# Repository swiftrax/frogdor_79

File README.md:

### I provide this keyboard without liability and without any guarantees regarding functionality, as expressed in the Creative Commons license under which all of these PCBs are licensed.

KiCad and Fusion360 files are included 

Tested Working on USB 2.0

QMK Can be found in my fork

# Supported Layouts

# Images
[Imgur Album](https://imgur.com/a/08Liv0p)

# Case
[M3 Spacers](https://www.mcmaster.com/94868a162) x 4 

[M3 Screws](https://www.mcmaster.com/93070a057) 1 pack 

Reccomended Manufacturers for cases: **Ponoko for Acrylic, SendCutSend for Metal** 

Plate x 1 3mm Acrylic 

Midlayer x 2 3mm Acrylic 

Backplate x 1 3mm Acrylic 

*Note if using an aluminum plate use O-rings as a spacer

# QMK
[Keyboard](https://github.com/swiftrax/qmk_firmware/tree/master/keyboards/frogdor)

`make frogdor:default`

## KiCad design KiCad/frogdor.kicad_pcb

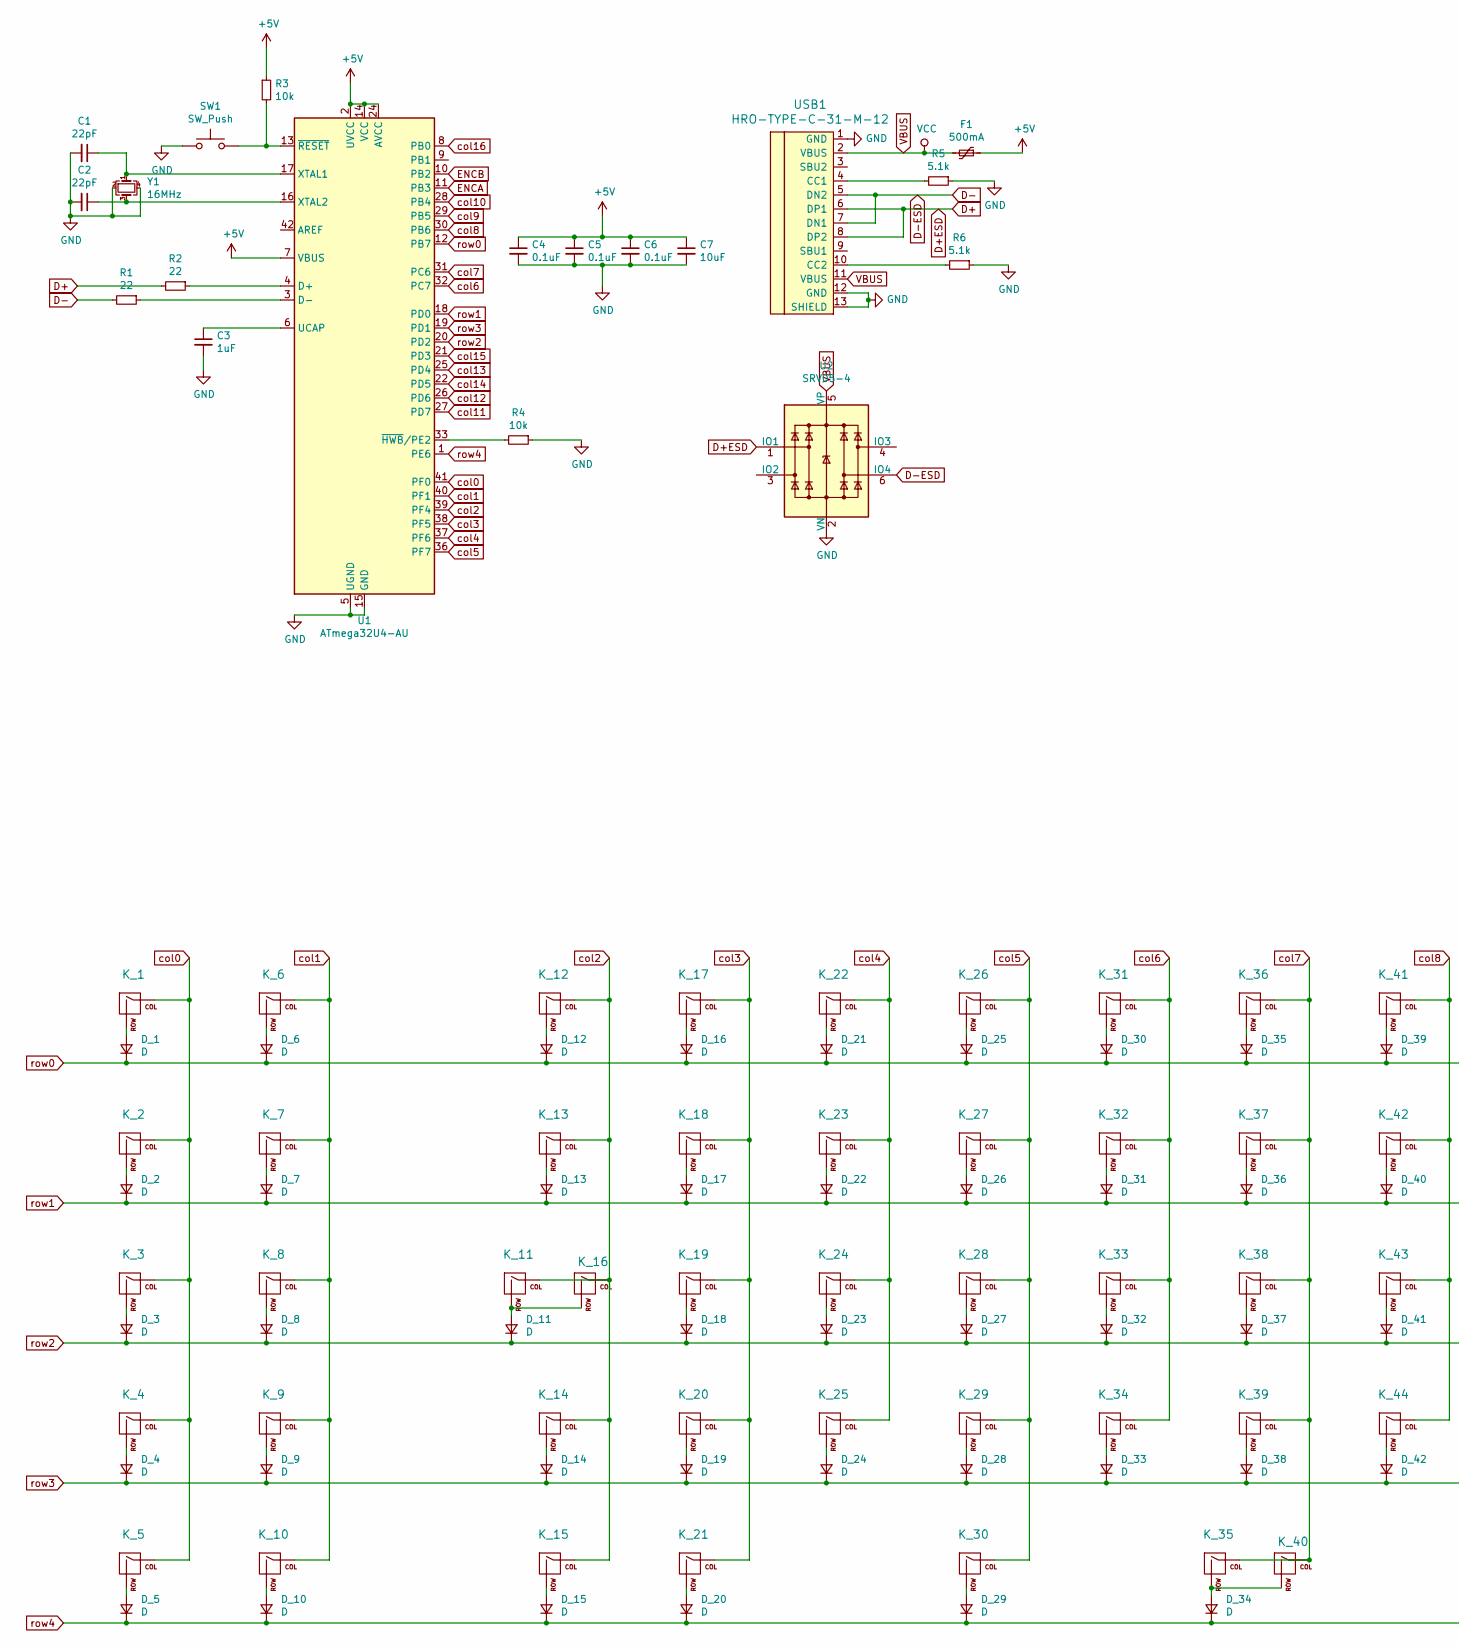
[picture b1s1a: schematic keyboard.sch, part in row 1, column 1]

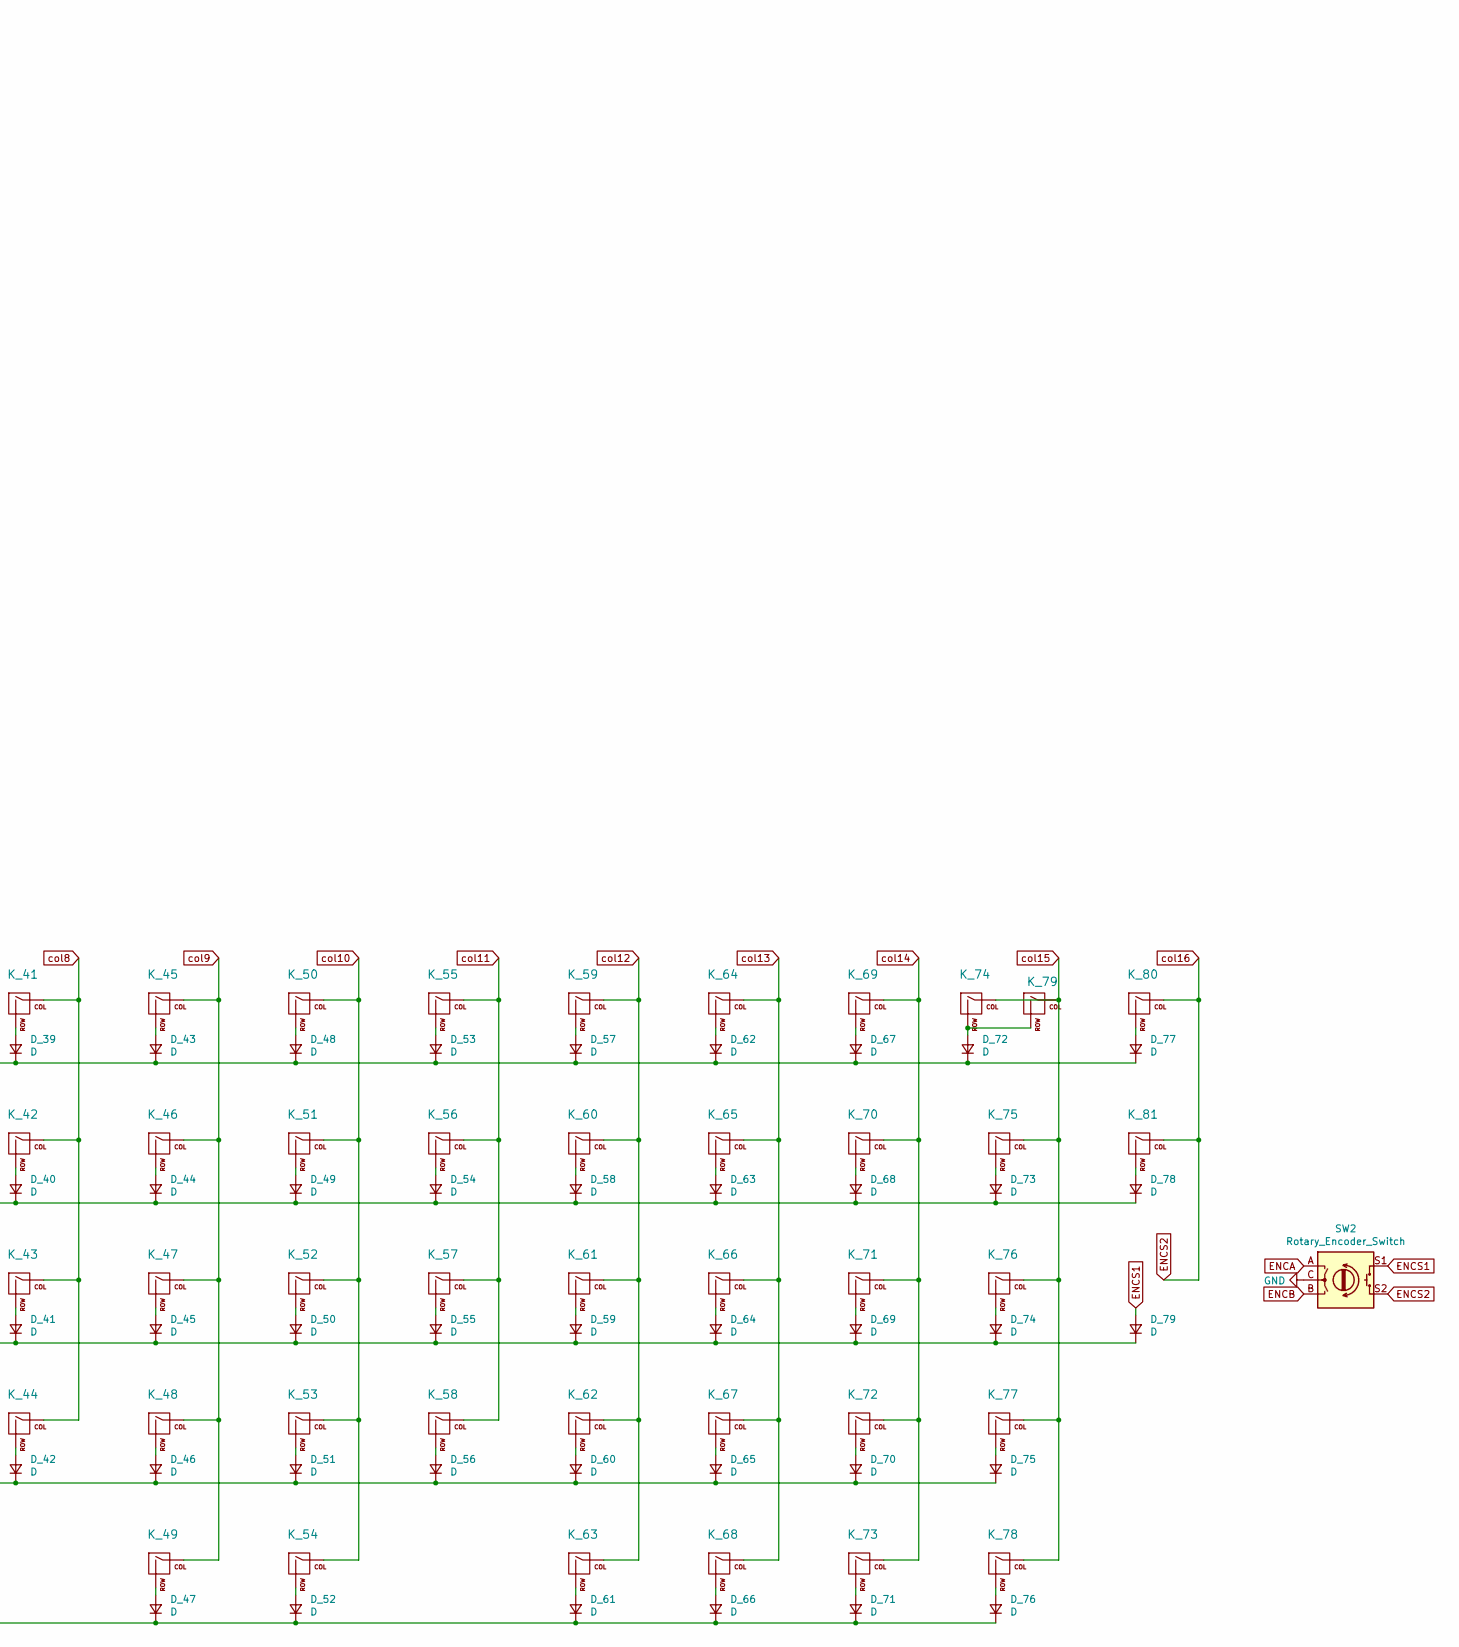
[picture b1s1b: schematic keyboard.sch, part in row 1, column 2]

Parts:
C1, C2: 22pF; C_0805_2012Metric
C3: 1uF; C_0805_2012Metric
C4, C5, C6: 0.1uF; C_0805_2012Metric
C7: 10uF; C_0805_2012Metric
D_1, D_2, D_3, D_4, D_5, D_6, D_7, D_8, D_9, D_10, D_11, D_12, D_13, D_14, D_15, D_16, D_17, D_18, D_19, D_20, D_21, D_22, D_23, D_24, D_25, D_26, D_27, D_28, D_29, D_30, D_31, D_32, D_33, D_34, D_35, D_36, D_37, D_38, D_39, D_40, D_41, D_42, D_43, D_44, D_45, D_46, D_47, D_48, D_49, D_50, D_51, D_52, D_53, D_54, D_55, D_56, D_57, D_58, D_59, D_60, D_61, D_62, D_63, D_64, D_65, D_66, D_67, D_68, D_69, D_70, D_71, D_72, D_73, D_74, D_75, D_76, D_77, D_78, D_79: D; D_SOD-123
F1: 500mA; Fuse_1206_3216Metric
K_1, K_2, K_3, K_4, K_5, K_6, K_7, K_8, K_9, K_10, K_12, K_17, K_18, K_19, K_20, K_22, K_23, K_24, K_25, K_26, K_27, K_28, K_29, K_31, K_32, K_33, K_34, K_36, K_37, K_38, K_39, K_41, K_42, K_43, K_44, K_45, K_46, K_47, K_48, K_50, K_51, K_52, K_53, K_55, K_56, K_57, K_58, K_59, K_60, K_61, K_62, K_64, K_65, K_66, K_68, K_69, K_70, K_72, K_73, K_74, K_76, K_77, K_78, K_80, K_81: KEYSW; MXOnly-1U-NoLED
K_11, K_15, K_21, K_35, K_54, K_63: KEYSW; MXOnly-1.25U-NoLED
K_13, K_75: KEYSW; MXOnly-1.5U-NoLED
K_14, K_49, K_71: KEYSW; MXOnly-2.25U-NoLED
K_16: KEYSW; MXOnly-1.75U-NoLED
K_30: KEYSW; MXOnly-2.75U-NoLED
K_40: KEYSW; MXOnly-6.25U-NoLED
K_67, K_79: KEYSW; MXOnly-2U-NoLED
R1, R2: 22; R_0805_2012Metric
R3, R4: 10k; R_0805_2012Metric
R5, R6: 5.1k; R_0805_2012Metric
SW1: SW_Push; SKQG-1155865
SW2: Rotary_Encoder_Switch; RotaryEncoder_EC11
U1: ATmega32U4-AU; TQFP-44_10x10mm_P0.8mm
U2: SRV05-4; SOT-23-6
USB1: HRO-TYPE-C-31-M-12; HRO-TYPE-C-31-M-12-HandSoldering
Y1: 16MHz; Crystal_SMD_3225-4Pin_3.2x2.5mm

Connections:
+5V: C4.1, C5.1, C6.1, C7.1, F1.1, R3.1, U1.2 (UVCC), U1.7 (VBUS), U1.14 (VCC), U1.24 (AVCC), U1.34 (VCC), U1.44 (AVCC)
D+: R2.2, U2.1 (IO1), USB1.6 (DP1), USB1.8 (DP2)
D-: R1.2, U2.6 (IO4), USB1.5 (DN2), USB1.7 (DN1)
ENCA: SW2.A, U1.11 (PB3)
ENCB: SW2.B, U1.10 (PB2)
ENCS1: D_79.2 (A), SW2.S1
ENCS2: K_80.1 (COL), K_81.1 (COL), SW2.S2, U1.8 (PB0)
GND: C1.2, C2.2, C3.2, C4.2, C5.2, C6.2, C7.2, R4.1, R5.1, R6.1, SW1.1, SW2.C, U1.5 (UGND), U1.15 (GND), U1.23 (GND), U1.35 (GND), U1.43 (GND), U2.2 (VN), USB1.1 (GND), USB1.12 (GND), USB1.13 (SHIELD), Y1.2, Y1.4
unnamed: C1.1, U1.17 (XTAL1), Y1.1
unnamed: C2.1, U1.16 (XTAL2), Y1.3
unnamed: C3.1, U1.6 (UCAP)
unnamed: D_1.2 (A), K_1.2 (ROW)
unnamed: D_2.2 (A), K_2.2 (ROW)
unnamed: D_3.2 (A), K_3.2 (ROW)
unnamed: D_4.2 (A), K_4.2 (ROW)
unnamed: D_5.2 (A), K_5.2 (ROW)
unnamed: D_6.2 (A), K_6.2 (ROW)
unnamed: D_7.2 (A), K_7.2 (ROW)
unnamed: D_8.2 (A), K_8.2 (ROW)
unnamed: D_9.2 (A), K_9.2 (ROW)
unnamed: D_10.2 (A), K_10.2 (ROW)
unnamed: D_11.2 (A), K_11.2 (ROW), K_16.2 (ROW)
unnamed: D_12.2 (A), K_12.2 (ROW)
unnamed: D_13.2 (A), K_13.2 (ROW)
unnamed: D_14.2 (A), K_14.2 (ROW)
unnamed: D_15.2 (A), K_15.2 (ROW)
unnamed: D_16.2 (A), K_17.2 (ROW)
unnamed: D_17.2 (A), K_18.2 (ROW)
unnamed: D_18.2 (A), K_19.2 (ROW)
unnamed: D_19.2 (A), K_20.2 (ROW)
unnamed: D_20.2 (A), K_21.2 (ROW)
unnamed: D_21.2 (A), K_22.2 (ROW)
unnamed: D_22.2 (A), K_23.2 (ROW)
unnamed: D_23.2 (A), K_24.2 (ROW)
unnamed: D_24.2 (A), K_25.2 (ROW)
unnamed: D_25.2 (A), K_26.2 (ROW)
unnamed: D_26.2 (A), K_27.2 (ROW)
unnamed: D_27.2 (A), K_28.2 (ROW)
unnamed: D_28.2 (A), K_29.2 (ROW)
unnamed: D_29.2 (A), K_30.2 (ROW)
unnamed: D_30.2 (A), K_31.2 (ROW)
unnamed: D_31.2 (A), K_32.2 (ROW)
unnamed: D_32.2 (A), K_33.2 (ROW)
unnamed: D_33.2 (A), K_34.2 (ROW)
unnamed: D_34.2 (A), K_35.2 (ROW), K_40.2 (ROW)
unnamed: D_35.2 (A), K_36.2 (ROW)
unnamed: D_36.2 (A), K_37.2 (ROW)
unnamed: D_37.2 (A), K_38.2 (ROW)
unnamed: D_38.2 (A), K_39.2 (ROW)
unnamed: D_39.2 (A), K_41.2 (ROW)
unnamed: D_40.2 (A), K_42.2 (ROW)
unnamed: D_41.2 (A), K_43.2 (ROW)
unnamed: D_42.2 (A), K_44.2 (ROW)
unnamed: D_43.2 (A), K_45.2 (ROW)
unnamed: D_44.2 (A), K_46.2 (ROW)
unnamed: D_45.2 (A), K_47.2 (ROW)
unnamed: D_46.2 (A), K_48.2 (ROW)
unnamed: D_47.2 (A), K_49.2 (ROW)
unnamed: D_48.2 (A), K_50.2 (ROW)
unnamed: D_49.2 (A), K_51.2 (ROW)
unnamed: D_50.2 (A), K_52.2 (ROW)
unnamed: D_51.2 (A), K_53.2 (ROW)
unnamed: D_52.2 (A), K_54.2 (ROW)
unnamed: D_53.2 (A), K_55.2 (ROW)
unnamed: D_54.2 (A), K_56.2 (ROW)
unnamed: D_55.2 (A), K_57.2 (ROW)
unnamed: D_56.2 (A), K_58.2 (ROW)
unnamed: D_57.2 (A), K_59.2 (ROW)
unnamed: D_58.2 (A), K_60.2 (ROW)
unnamed: D_59.2 (A), K_61.2 (ROW)
unnamed: D_60.2 (A), K_62.2 (ROW)
unnamed: D_61.2 (A), K_63.2 (ROW)
unnamed: D_62.2 (A), K_64.2 (ROW)
unnamed: D_63.2 (A), K_65.2 (ROW)
unnamed: D_64.2 (A), K_66.2 (ROW)
unnamed: D_65.2 (A), K_67.2 (ROW)
unnamed: D_66.2 (A), K_68.2 (ROW)
unnamed: D_67.2 (A), K_69.2 (ROW)
unnamed: D_68.2 (A), K_70.2 (ROW)
unnamed: D_69.2 (A), K_71.2 (ROW)
unnamed: D_70.2 (A), K_72.2 (ROW)
unnamed: D_71.2 (A), K_73.2 (ROW)
unnamed: D_72.2 (A), K_74.2 (ROW), K_79.2 (ROW)
unnamed: D_73.2 (A), K_75.2 (ROW)
unnamed: D_74.2 (A), K_76.2 (ROW)
unnamed: D_75.2 (A), K_77.2 (ROW)
unnamed: D_76.2 (A), K_78.2 (ROW)
unnamed: D_77.2 (A), K_80.2 (ROW)
unnamed: D_78.2 (A), K_81.2 (ROW)
unnamed: R1.1, U1.3 (D-)
unnamed: R2.1, U1.4 (D+)
unnamed: R3.2, SW1.2, U1.13 (~RESET)
unnamed: R4.2, U1.33 (~HWB~/PE2)
unnamed: R5.2, USB1.4 (CC1)
unnamed: R6.2, USB1.10 (CC2)
VBUS: F1.2, U2.5 (VP), USB1.2 (VBUS), USB1.11 (VBUS)
col0: K_1.1 (COL), K_2.1 (COL), K_3.1 (COL), K_4.1 (COL), K_5.1 (COL), U1.41 (PF0)
col1: K_6.1 (COL), K_7.1 (COL), K_8.1 (COL), K_9.1 (COL), K_10.1 (COL), U1.40 (PF1)
col2: K_11.1 (COL), K_12.1 (COL), K_13.1 (COL), K_14.1 (COL), K_15.1 (COL), K_16.1 (COL), U1.39 (PF4)
col3: K_17.1 (COL), K_18.1 (COL), K_19.1 (COL), K_20.1 (COL), K_21.1 (COL), U1.38 (PF5)
col4: K_22.1 (COL), K_23.1 (COL), K_24.1 (COL), K_25.1 (COL), U1.37 (PF6)
col5: K_26.1 (COL), K_27.1 (COL), K_28.1 (COL), K_29.1 (COL), K_30.1 (COL), U1.36 (PF7)
col6: K_31.1 (COL), K_32.1 (COL), K_33.1 (COL), K_34.1 (COL), U1.32 (PC7)
col7: K_35.1 (COL), K_36.1 (COL), K_37.1 (COL), K_38.1 (COL), K_39.1 (COL), K_40.1 (COL), U1.31 (PC6)
col8: K_41.1 (COL), K_42.1 (COL), K_43.1 (COL), K_44.1 (COL), U1.30 (PB6)
col9: K_45.1 (COL), K_46.1 (COL), K_47.1 (COL), K_48.1 (COL), K_49.1 (COL), U1.29 (PB5)
col10: K_50.1 (COL), K_51.1 (COL), K_52.1 (COL), K_53.1 (COL), K_54.1 (COL), U1.28 (PB4)
col11: K_55.1 (COL), K_56.1 (COL), K_57.1 (COL), K_58.1 (COL), U1.27 (PD7)
col12: K_59.1 (COL), K_60.1 (COL), K_61.1 (COL), K_62.1 (COL), K_63.1 (COL), U1.26 (PD6)
col13: K_64.1 (COL), K_65.1 (COL), K_66.1 (COL), K_67.1 (COL), K_68.1 (COL), U1.25 (PD4)
col14: K_69.1 (COL), K_70.1 (COL), K_71.1 (COL), K_72.1 (COL), K_73.1 (COL), U1.22 (PD5)
col15: K_74.1 (COL), K_75.1 (COL), K_76.1 (COL), K_77.1 (COL), K_78.1 (COL), K_79.1 (COL), U1.21 (PD3)
row0: D_1.1 (K), D_6.1 (K), D_12.1 (K), D_16.1 (K), D_21.1 (K), D_25.1 (K), D_30.1 (K), D_35.1 (K), D_39.1 (K), D_43.1 (K), D_48.1 (K), D_53.1 (K), D_57.1 (K), D_62.1 (K), D_67.1 (K), D_72.1 (K), D_77.1 (K), U1.12 (PB7)
row1: D_2.1 (K), D_7.1 (K), D_13.1 (K), D_17.1 (K), D_22.1 (K), D_26.1 (K), D_31.1 (K), D_36.1 (K), D_40.1 (K), D_44.1 (K), D_49.1 (K), D_54.1 (K), D_58.1 (K), D_63.1 (K), D_68.1 (K), D_73.1 (K), D_78.1 (K), U1.18 (PD0)
row2: D_3.1 (K), D_8.1 (K), D_11.1 (K), D_18.1 (K), D_23.1 (K), D_27.1 (K), D_32.1 (K), D_37.1 (K), D_41.1 (K), D_45.1 (K), D_50.1 (K), D_55.1 (K), D_59.1 (K), D_64.1 (K), D_69.1 (K), D_74.1 (K), D_79.1 (K), U1.20 (PD2)
row3: D_4.1 (K), D_9.1 (K), D_14.1 (K), D_19.1 (K), D_24.1 (K), D_28.1 (K), D_33.1 (K), D_38.1 (K), D_42.1 (K), D_46.1 (K), D_51.1 (K), D_56.1 (K), D_60.1 (K), D_65.1 (K), D_70.1 (K), D_75.1 (K), U1.19 (PD1)
row4: D_5.1 (K), D_10.1 (K), D_15.1 (K), D_20.1 (K), D_29.1 (K), D_34.1 (K), D_47.1 (K), D_52.1 (K), D_61.1 (K), D_66.1 (K), D_71.1 (K), D_76.1 (K), U1.1 (PE6)

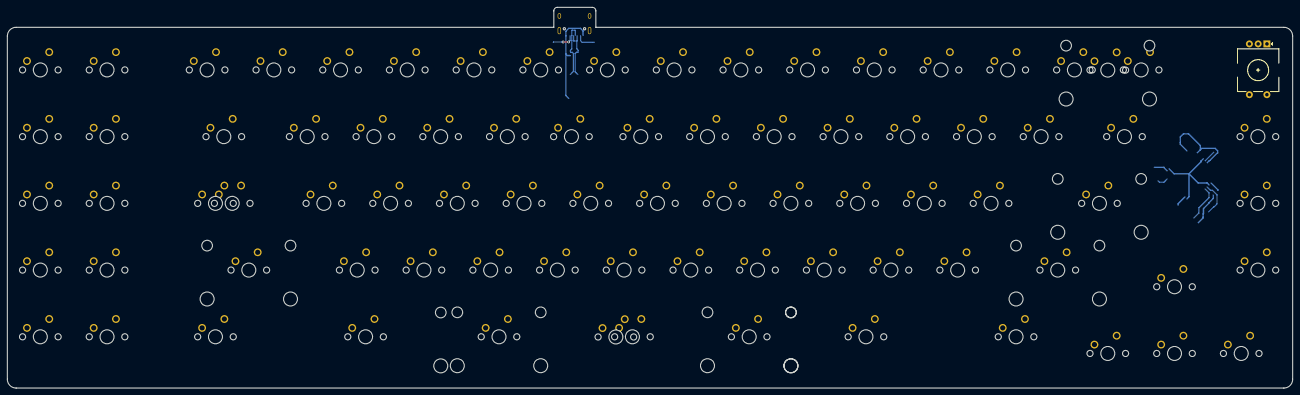
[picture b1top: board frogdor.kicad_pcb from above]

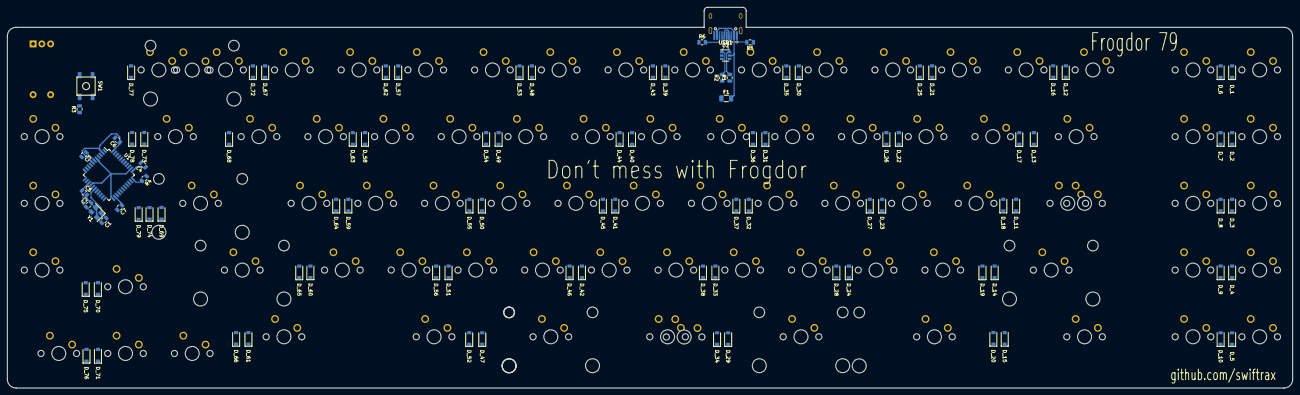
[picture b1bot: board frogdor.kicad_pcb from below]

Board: 2 copper layers, 367.0 x 108.7 mm, 180 parts (98 on the bottom side), 117 nets.

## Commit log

2020-03-11 Remove Tracks
2020-03-16 Add Files needed
2020-03-16 Create LICENSE
2020-04-13 Update Case
2020-04-14 Remove Plates.kicad
2020-04-15 Add DXF and EPS files for the case
2020-05-28 Add PCB renders
